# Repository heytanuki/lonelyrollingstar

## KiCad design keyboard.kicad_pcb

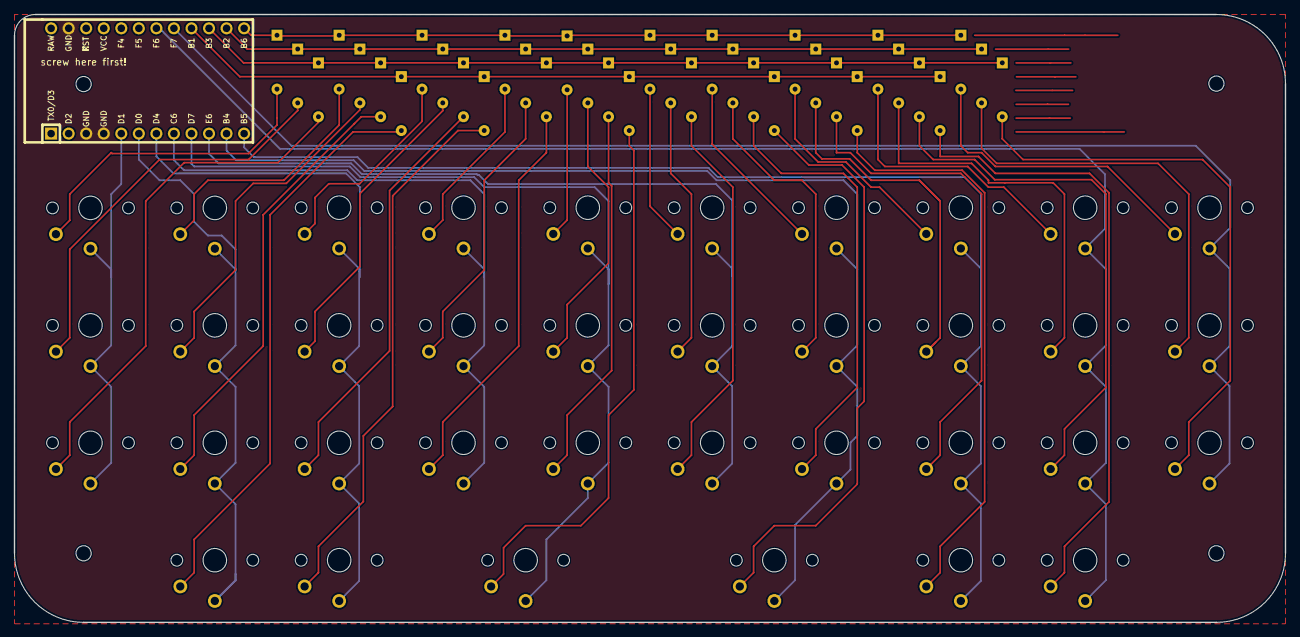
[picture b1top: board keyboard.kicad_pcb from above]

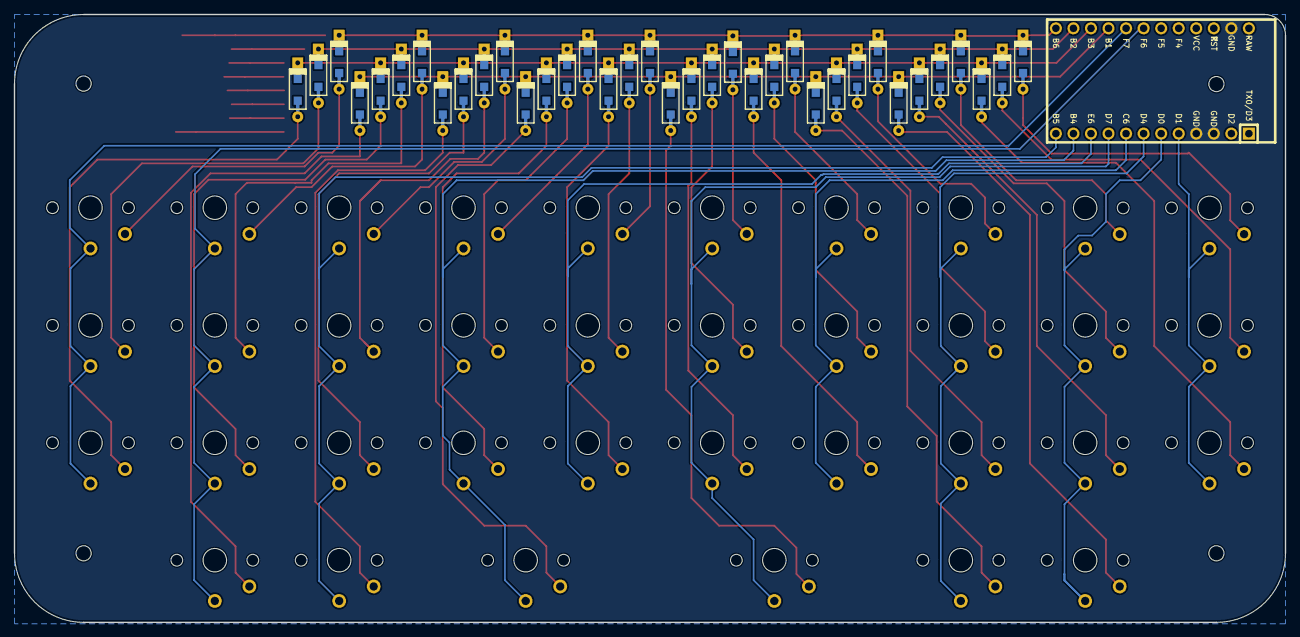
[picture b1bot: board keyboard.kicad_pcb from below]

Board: 2 copper layers, 184.0 x 88.0 mm, 74 parts (36 on the bottom side), 51 nets.

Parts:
D_1: D; D_SOD123_axial
D_A1: D; D_SOD123_axial
D_ALT1: D; D_SOD123_axial
D_B1: D; D_SOD123_axial
D_C1: D; D_SOD123_axial
D_COMMA1: D; D_SOD123_axial
D_D1: D; D_SOD123_axial
D_DOT1: D; D_SOD123_axial
D_E1: D; D_SOD123_axial
D_ENTER1: D; D_SOD123_axial
D_F1: D; D_SOD123_axial
D_G1: D; D_SOD123_axial
D_H1: D; D_SOD123_axial
D_I1: D; D_SOD123_axial
D_J1: D; D_SOD123_axial
D_K1: D; D_SOD123_axial
D_L1: D; D_SOD123_axial
D_M1: D; D_SOD123_axial
D_META1: D; D_SOD123_axial
D_N1: D; D_SOD123_axial
D_O1: D; D_SOD123_axial
D_Q1: D; D_SOD123_axial
D_R1: D; D_SOD123_axial
D_S1: D; D_SOD123_axial
D_SEMIC1: D; D_SOD123_axial
D_SPACE1, D_SPACE2, D_SPACE3, D_SPACE4: D; D_SOD123_axial
D_T1: D; D_SOD123_axial
D_U1: D; D_SOD123_axial
D_V1: D; D_SOD123_axial
D_W1: D; D_SOD123_axial
D_X1: D; D_SOD123_axial
D_Y1: D; D_SOD123_axial
D_Z1: D; D_SOD123_axial
K_1: KEYSW; Choc-1u-solder
K_A1: KEYSW; Choc-1u-solder
K_ALT1: KEYSW; Choc-1u-solder
K_B1: KEYSW; Choc-1u-solder
K_C1: KEYSW; Choc-1u-solder
K_COMMA1: KEYSW; Choc-1u-solder
K_D1: KEYSW; Choc-1u-solder
K_DOT1: KEYSW; Choc-1u-solder
K_E1: KEYSW; Choc-1u-solder
K_ENTER1: KEYSW; Choc-1u-solder
K_F1: KEYSW; Choc-1u-solder
K_G1: KEYSW; Choc-1u-solder
K_H1: KEYSW; Choc-1u-solder
K_I1: KEYSW; Choc-1u-solder
K_J1: KEYSW; Choc-1u-solder
K_K1: KEYSW; Choc-1u-solder
K_L1: KEYSW; Choc-1u-solder
K_M1: KEYSW; Choc-1u-solder
K_META1: KEYSW; Choc-1u-solder
K_N1: KEYSW; Choc-1u-solder
K_O1: KEYSW; Choc-1u-solder
K_Q1: KEYSW; Choc-1u-solder
K_R1: KEYSW; Choc-1u-solder
K_S1: KEYSW; Choc-1u-solder
K_SEMIC1: KEYSW; Choc-1u-solder
K_SPACE1, K_SPACE2, K_SPACE3, K_SPACE4: KEYSW; Choc-1u-solder
K_T1: KEYSW; Choc-1u-solder
K_U1: KEYSW; Choc-1u-solder
K_V1: KEYSW; Choc-1u-solder
K_W1: KEYSW; Choc-1u-solder
K_X1: KEYSW; Choc-1u-solder
K_Y1: KEYSW; Choc-1u-solder
K_Z1: KEYSW; Choc-1u-solder
U1: ProMicro; ArduinoProMicro
screw here first!: MountingHole_2.2mm_M2

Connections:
GND: U1.3, U1.4, U1.23
unnamed: D_1.2, K_1.2
unnamed: D_A1.2, K_A1.2
unnamed: D_ALT1.2, K_ALT1.2
unnamed: D_B1.2, K_B1.2
unnamed: D_C1.2, K_C1.2
unnamed: D_COMMA1.2, K_COMMA1.2
unnamed: D_D1.2, K_D1.2
unnamed: D_DOT1.2, K_DOT1.2
unnamed: D_E1.2, K_E1.2
unnamed: D_ENTER1.2, K_ENTER1.2
unnamed: D_F1.2, K_F1.2
unnamed: D_G1.2, K_G1.2
unnamed: D_H1.2, K_H1.2
unnamed: D_I1.2, K_I1.2
unnamed: D_J1.2, K_J1.2
unnamed: D_K1.2, K_K1.2
unnamed: D_L1.2, K_L1.2
unnamed: D_M1.2, K_M1.2
unnamed: D_META1.2, K_META1.2
unnamed: D_N1.2, K_N1.2
unnamed: D_O1.2, K_O1.2
unnamed: D_Q1.2, K_Q1.2
unnamed: D_R1.2, K_R1.2
unnamed: D_S1.2, K_S1.2
unnamed: D_SEMIC1.2, K_SEMIC1.2
unnamed: D_SPACE1.2, K_SPACE1.2
unnamed: D_SPACE2.2, K_SPACE2.2
unnamed: D_SPACE3.2, K_SPACE3.2
unnamed: D_SPACE4.2, K_SPACE4.2
unnamed: D_T1.2, K_T1.2
unnamed: D_U1.2, K_U1.2
unnamed: D_V1.2, K_V1.2
unnamed: D_W1.2, K_W1.2
unnamed: D_X1.2, K_X1.2
unnamed: D_Y1.2, K_Y1.2
unnamed: D_Z1.2, K_Z1.2
col0: K_A1.1, K_Q1.1, K_Z1.1, U1.5
col1: K_META1.1, K_S1.1, K_W1.1, K_X1.1, U1.6
col2: K_ALT1.1, K_C1.1, K_D1.1, K_E1.1, U1.7
col3: K_F1.1, K_R1.1, K_V1.1, U1.8
col4: K_B1.1, K_ENTER1.1, K_G1.1, K_T1.1, U1.9
col5: K_H1.1, K_N1.1, K_Y1.1, U1.10
col6: K_J1.1, K_M1.1, K_SPACE3.1, K_U1.1, U1.11
col7: K_1.1, K_COMMA1.1, K_I1.1, K_K1.1, U1.12
col8: K_DOT1.1, K_L1.1, K_O1.1, K_SEMIC1.1, U1.18
col9: K_SPACE1.1, K_SPACE2.1, K_SPACE4.1, U1.17
row0: D_E1.1, D_I1.1, D_O1.1, D_Q1.1, D_R1.1, D_SPACE4.1, D_T1.1, D_U1.1, D_W1.1, D_Y1.1, U1.13
row1: D_A1.1, D_D1.1, D_F1.1, D_G1.1, D_H1.1, D_J1.1, D_K1.1, D_L1.1, D_S1.1, D_SPACE1.1, U1.14
row2: D_B1.1, D_C1.1, D_COMMA1.1, D_DOT1.1, D_M1.1, D_N1.1, D_SPACE2.1, D_V1.1, D_X1.1, D_Z1.1, U1.15
row3: D_1.1, D_ALT1.1, D_ENTER1.1, D_META1.1, D_SEMIC1.1, D_SPACE3.1, U1.16

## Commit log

2021-07-23 add qmk and readme
